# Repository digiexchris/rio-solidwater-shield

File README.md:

# rio-SolidWater-Sheild
6 Axis LinuxCNC-RIO Raspberry-PI FPGA-Hat based heavily on rio-IceShield, designed for stepper motors.
**experimental**

Nearly a 100% pin compatible rework of the rio-iceshield using single sided SMD, so that it can be inexpensively manufactured by JLCPCB or other parts fab houses. Some parts have been changed to parts that are available through the fab house, so that all SMD components can be assembled at the fab house.

Maximum step rate is theoretically 500khz due to the minimum rise and fall time of the  though this has not been tested much more than 

## Hardware

- Tested on a Raspberry Pi 4b with the Touchy and Axis UIs. Axis is a bit slow for a pi4 though, I recommend only using it for initial calibration and trying Touchy or another UI.
- If you don't use it on a Pi 4b, you will have to provide a 5mhz clock signal on the pi GPIO header pin 7.
- The 24v power jack is ONLY for input, output, and stepper connections, it will not power the board or pi. You can supply any voltage you wish on there, up to a maximum of 50v, which is the limit of the ULN2803A line driver.
- You can select if the inputs and outputs (not including stepper outputs) supply 5v from the pi or external power from the jack labelled 24v through the isel1 jumper. Short the middle pin to either the top or bottom pin, labelled on the top side of the board. Both 5v and external power is available on all stepper headers. 
- The connectors used are JST-XH 2.54mm pitch. Any 2.54mm or 0.1" pitch connector or pin header will work.

## software / gateware
Requires:
https://github.com/multigcs/riocore

## Ordering:

Production output files are provided in the Production-Outputs directory. JLCPCB required a few small replacements due limits in stock, so the parts that were selected during the assembly step are included in bom.xls, and bom.xls should be able to be uploaded to JLCPCB directly during the assembly ordering step. Select ONLY the top side for assembly, and Economy assembly is fine. The positions.csv is included as well.

Don't be alarmed if during the parts placement confirmation step the parts appear rotated, the fab house will place them in their correct orientation. It's recommended to select "Confirm Parts Placement" so they can send you the generated final placement once they've analyzed it. The parts that I either could not see or needed to fix in the ordering preview ended up corrected when they emailed me the production file before production started.

The gerber files are in the zip file in the same directory. It is a 4 layer board.

There is a minimum pcb order of 5 and a minimum assembly order of 2, and production and assembly cost for me was approximately $50 CAD for 2 boards in 2024. You end up with 3 spare unpopulated boards to use as coasters!

## Usage:

- Setup a https://github.com/multigcs/riocore as normal according to the instructions there.
- Copy the riocore/config/IceShield/config.json
- Generate and compile the config.
- Navigate to the Output dir, and run sudo ./spiflash.sh ./rio.bin
If successful, you probably will see a solid green light on the board.
If not, you may need to add yourself to appropriate SPI groups, or enable SPI on the raspberry pi you're using. Post an issue here if you have trouble with this, I likely have details available on my reference hardware.
This requires a clock signal from the raspberry pi on GPIO header pin 7. There are a few ways to do this, but I did it by installing the WiringPi tooling https://github.com/WiringPi/WiringPi and then executing
```
gpio mode 7 clock
gpio clock 7 5000000
```
You may add this to your Output/IceShield/LinuxCNC/start.sh to automate this.
If that was successful, the green LED should start blinking, assuming your config has the default "blink" plugin setup.

Proceed to setup LinuxCNC as normal according to https://github.com/multigcs/riocore

## Forum
English: https://forum.linuxcnc.org/18-computer/49142-linuxcnc-rio-realtimeio-for-linuxcnc-based-on-fpga-ice40-ecp5

## Derived From
https://github.com/multigcs/rio-iceshield

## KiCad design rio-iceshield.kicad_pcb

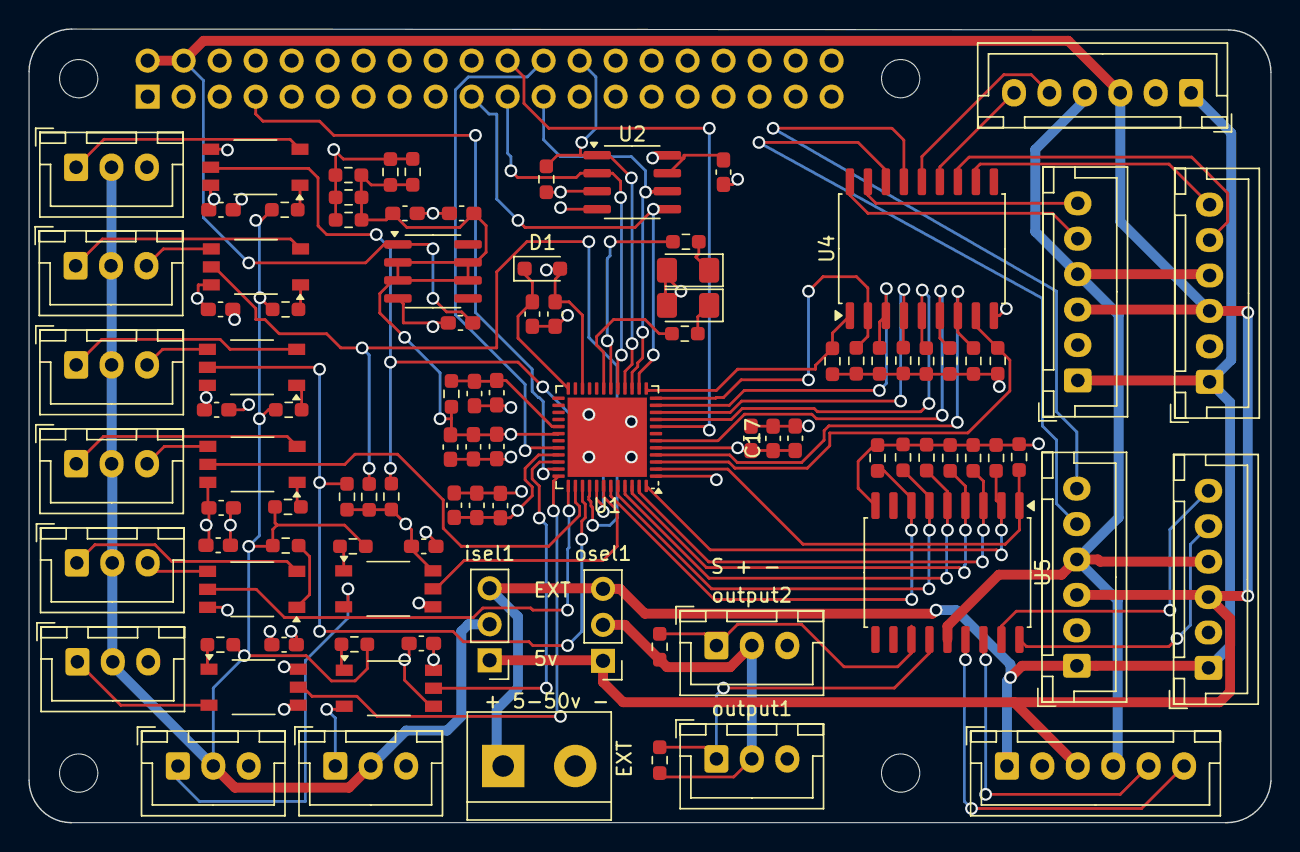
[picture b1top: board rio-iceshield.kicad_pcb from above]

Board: 4 copper layers, 87.6 x 56.0 mm, 102 parts (1 on the bottom side), 74 nets.

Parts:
C1, C3: 4u7; C_0603_1608Metric_Pad1.08x0.95mm_HandSolder
C2, C13, C17: 10n; C_0603_1608Metric_Pad1.08x0.95mm_HandSolder
C4, C5, C6, C7, C8, C9, C10, C14, C16, C18, C19, C20, C21, C22, C23, C24, C25: 100n; C_0603_1608Metric_Pad1.08x0.95mm_HandSolder
C11: 10u; C_0603_1608Metric_Pad1.08x0.95mm_HandSolder
C12, C15: 1u; C_0603_1608Metric_Pad1.08x0.95mm_HandSolder
D1: 1N4148WS; D_SOD-323_HandSoldering
D2, D3: LED; LED_1206_3216Metric_Pad1.42x1.75mm_HandSolder
EXT: Screw_Terminal_01x02; TerminalBlock_bornier-2_P5.08mm
J2, J3, J4, J5, J6: Conn_01x06; JST_XH_B6B-XH-A_1x06_P2.50mm_Vertical
Jo1: Conn_01x06; JST_XH_B6B-XH-A_1x06_P2.50mm_Vertical
MH1, MH2, MH3, MH4: MountingHole_2.7mm_M2.5
R1: 100; R_0603_1608Metric_Pad0.98x0.95mm_HandSolder
R2, R3, R4, R5, R6, R7, R8, R9: 3K3; R_0603_1608Metric_Pad0.98x0.95mm_HandSolder
R10, R11: 1k; R_0603_1608Metric_Pad0.98x0.95mm_HandSolder
R12: 10k; R_0603_1608Metric_Pad0.98x0.95mm_HandSolder
R13, R14, R15, R16, R17, R18, R19, R20, R21, R22, R23, R24, R25, R26, R27: 20k; R_0603_1608Metric_Pad0.98x0.95mm_HandSolder
R28, R29, R30: 20K; R_0603_1608Metric_Pad0.98x0.95mm_HandSolder
R31, R32: 3k3; R_0603_1608Metric_Pad0.98x0.95mm_HandSolder
R33, R34, R35, R36, R37: 1k2; R_0603_1608Metric_Pad0.98x0.95mm_HandSolder
U1: ICE40UP5K-SG48ITR; QFN-48-1EP_7x7mm_P0.5mm_EP5.6x5.6mm
U2: AT25SF041B-SHD 4 Mb; SOIC-8_3.9x4.9mm_P1.27mm
U4, U5: ULN2803A; SOP-18_7.495x11.515mm_P1.27mm
U6, U15, U16, U17, U18, U19, U20, U21: ELM453-TA-V; MFSOP6-5_4.4x3.6mm_P1.27mm
U7: LM317LD13TR; SOIC-8_3.9x4.9mm_P1.27mm
input1, input2, input3, input4, input5, input6, input7, input8: Conn_01x03; JST_XH_B3B-XH-A_1x03_P2.50mm_Vertical
isel1: Conn_01x03; PinHeader_1x03_P2.54mm_Vertical
j1: GPIO; PinSocket_2x20_P2.54mm_Vertical
osel1: Conn_01x03; PinHeader_1x03_P2.54mm_Vertical
output1, output2: Conn_01x03; JST_XH_B3B-XH-A_1x03_P2.50mm_Vertical

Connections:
1v2: C2.1, C3.1, C12.1, C13.1, C14.1, C15.1, C16.1, C17.1, R1.1, R33.2, R34.2, R35.2, R36.2, R37.2, U1.5 (VCC), U1.30 (VCC), U7.2 (VO), U7.3 (VO), U7.6 (VO), U7.7 (VO)
2: R21.2, U1.2 (IOB_6a), U5.1 (I1)
2v5: C10.1, D1.1 (K), U1.24 (VPP_2V5)
3: R20.2, U1.3 (IOB_9b), U4.8 (I8)
3v3: C4.2, C5.2, C6.2, C7.2, C9.1, C18.1, C19.1, C20.1, C21.1, C22.1, C23.1, C24.1, C25.1, D1.2 (A), D2.2 (A), D3.2 (A), R12.1, R28.1, R29.1, R30.1, U1.1 (VCCIO_2), U1.22 (SPI_VCCIO1), U1.33 (VCCIO_0), U2.3 (~WP/IO2), U2.7 (~HOLD/IO3), U2.8 (VCC), U6.6, U15.6, U16.6, U17.6, U18.6, U19.6, U20.6, U21.6, j1.1, j1.17
4: R19.2, U1.4 (IOB_8a), U4.7 (I7)
5v: C1.1, J2.3, J3.3, J4.3, J5.3, J6.3, Jo1.3, U7.1 (VI), isel1.1, j1.2, j1.4, osel1.1
6: R18.2, U1.6 (IOB_13b), U4.6 (I6)
9: R17.2, U1.9 (IOB_16a), U4.5 (I5)
10: R16.2, U1.10 (IOB_18a), U4.4 (I4)
11: R15.2, U1.11 (IOB_20a), U4.3 (I3)
12: R14.2, U1.12 (IOB_22a), U4.2 (I2)
12v: EXT.1, J2.1, J3.1, J4.1, J5.1, J6.1, Jo1.1, isel1.3, osel1.3
13: R13.2, U1.13 (IOB_24a), U4.1 (I1)
18: R11.1, U1.18 (IOB_31b)
19: R10.1, U1.19 (IOB_29b)
32: U1.32 (IOT_43a), j1.24
34: U1.34 (IOT_44b), U21.5
35: U1.35 (IOT_46b_G0), j1.7
36: U1.36 (IOT_48b), U19.5
37: U1.37 (IOT_45a_G1), U18.5
38: U1.38 (IOT_50b), U17.5
39: R28.2, U1.39 (RGB0), U16.5
40: R29.2, U1.40 (RGB1), U15.5
41: R30.2, U1.41 (RGB2), U6.5
42: U1.42 (IOT_51a), U20.5
43: R27.2, U1.43 (IOT_49a), U5.7 (I7)
44: R26.2, U1.44 (IOB_3b_G6), U5.6 (I6)
45: R25.2, U1.45 (IOB_5b), U5.5 (I5)
46: R24.2, U1.46 (IOB_0a), U5.4 (I4)
47: R23.2, U1.47 (IOB_2a), U5.3 (I3)
48: R22.2, U1.48 (IOB_4a), U5.2 (I2)
CRESET: U1.8 (~CRESET), j1.22
unnamed: D2.1 (K), R11.2
unnamed: D3.1 (K), R10.2
unnamed: R2.1, U6.1
unnamed: R3.1, U15.1
unnamed: R4.1, U16.1
unnamed: R5.1, U17.1
unnamed: R6.1, U18.1
unnamed: R7.1, U19.1
unnamed: R8.1, U20.1
unnamed: R9.1, U21.1
unnamed: C8.1, C11.1, R1.2, U1.29 (VCCPLL)
unnamed: U6.3, input1.1
unnamed: U15.3, input2.1
unnamed: U16.3, input3.1
unnamed: U17.3, input4.1
unnamed: U18.3, input5.1
unnamed: U19.3, input6.1
unnamed: U20.3, input7.1
unnamed: U21.3, input8.1
SPI_CS1: R12.2, U1.16 (IOB_35b_SPI_SS), U2.1 (~CS), j1.26
SPI_MISO: U1.17 (IOB_33b_SPI_SI), U2.2 (SO/IO1), j1.21
SPI_MOSI: U1.14 (IOB_32a_SPI_SO), U2.5 (SI/IO0), j1.19
SPI_SCK: U1.15 (IOB_34a_SPI_SCK), U2.6 (SCK), j1.23
enable: J2.4, J3.4, J4.4, J5.4, J6.4, Jo1.4, U5.14 (O5)
gnd: C1.2, C2.2, C3.2, C4.1, C5.1, C6.1, C7.1, C8.2, C9.2, C10.2, C11.2, C12.2, C13.2, C14.2, C15.2, C16.2, C17.2, C18.2, C19.2, C20.2, C21.2, C22.2, C23.2, C24.2, C25.2, EXT.2, J2.2, J3.2, J4.2, J5.2, J6.2, Jo1.2, R13.1, R14.1, R15.1, R16.1, R17.1, R18.1, R19.1, R20.1, R21.1, R22.1, R23.1, R24.1, R25.1, R26.1, R27.1, R33.1, R34.1, R35.1, R36.1, R37.1, U1.49 (GND), U2.4 (GND), U4.9 (GND), U5.9 (GND), U6.4, U7.4 (ADJ), U15.4, U16.4, U17.4, U18.4, U19.4, U20.4, U21.4, input1.3, input2.3, input3.3, input4.3, input5.3, input6.3, input7.3, input8.3, j1.6, j1.9, j1.14, j1.20, j1.25, j1.30, j1.34, j1.39, output1.3, output2.3
in_power: R2.2, R3.2, R4.2, R5.2, R6.2, R7.2, R8.2, R9.2, input1.2, input2.2, input3.2, input4.2, input5.2, input6.2, input7.2, input8.2, isel1.2
j1_dir: Jo1.6, U4.17 (O2)
j1_step: Jo1.5, U4.18 (O1)
j2_dir: J2.6, U4.15 (O4)
j2_step: J2.5, U4.16 (O3)
j3_dir: J3.6, U4.13 (O6)
j3_step: J3.5, U4.14 (O5)
j4_dir: J4.6, U4.11 (O8)
j4_step: J4.5, U4.12 (O7)
j5_dir: J5.6, U5.17 (O2)
j5_step: J5.5, U5.18 (O1)
j6_dir: J6.6, U5.15 (O4)
j6_step: J6.5, U5.16 (O3)
out1: R31.1, U5.13 (O6), output1.1
out2: R32.1, U5.12 (O7), output2.1
out_power: R31.2, R32.2, osel1.2, output1.2, output2.2

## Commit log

2024-10-24 Fix missing clk line
2024-11-05 Documentation update
